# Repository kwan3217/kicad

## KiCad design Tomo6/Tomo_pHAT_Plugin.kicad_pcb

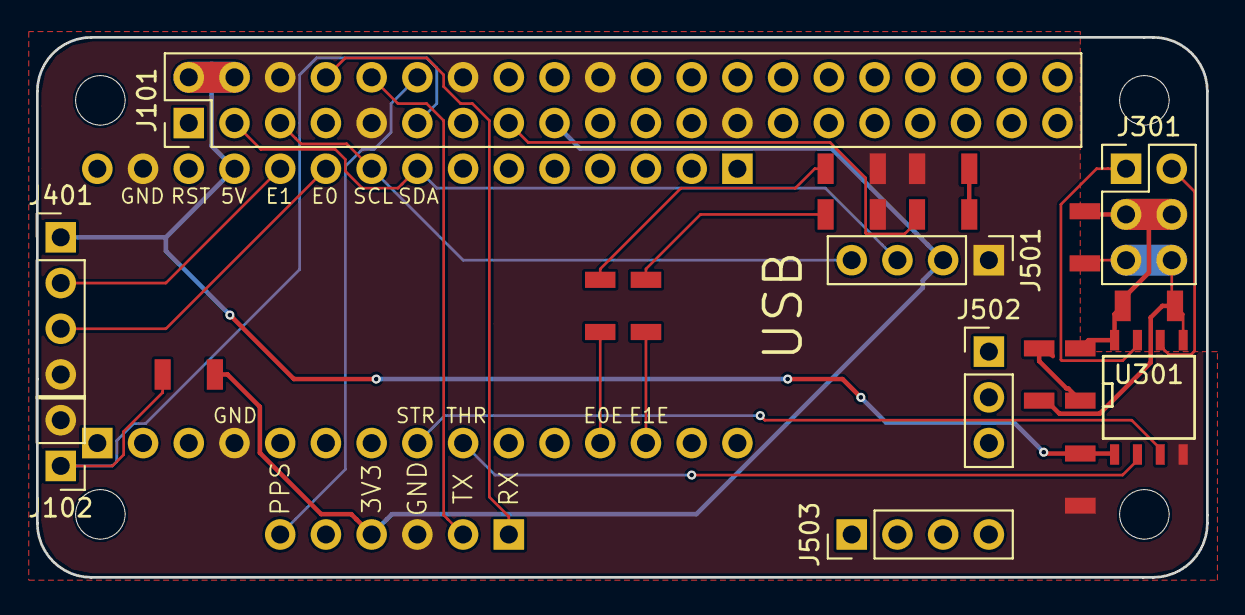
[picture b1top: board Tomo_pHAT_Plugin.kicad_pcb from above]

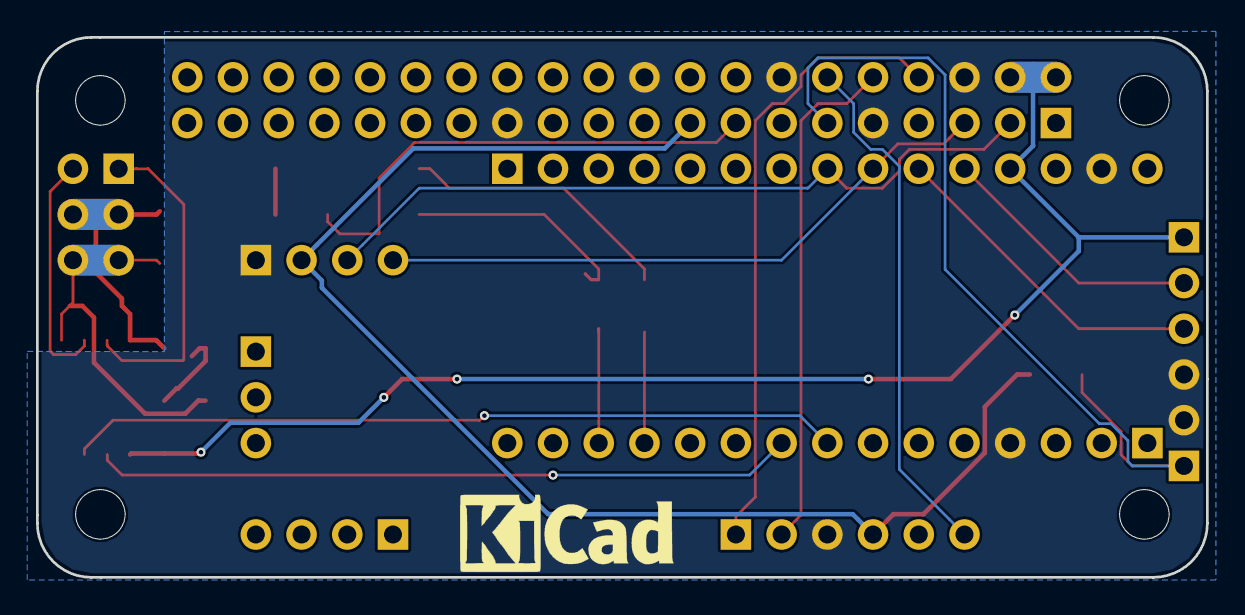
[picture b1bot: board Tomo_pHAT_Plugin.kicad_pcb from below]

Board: 2 copper layers, 65.0 x 30.0 mm, 28 parts (2 on the bottom side), 24 nets.

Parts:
1PIN, 1PIN#2, 1PIN#3, 1PIN#4: P***; 1pin
C301, C305: 100nF; SMD_1206
C308: 10uF; SMD_1206
D112: RED; D_1206
D308: BLUE; D_1206
D409: GREEN; D_1206
D410: YELLOW; D_1206
J101: RPi_GPIO; Pin_Header_Straight_2x20_Pitch2.54mm
J102: CONN_01X02; Socket_Strip_Straight_1x02_Pitch2.54mm
J301: CONN_02X03; Pin_Header_Straight_2x03_Pitch2.54mm
J401, J501, J503: CONN_01X04; Pin_Header_Straight_1x04_Pitch2.54mm
J502: CONN_01X03; Pin_Header_Straight_1x03_Pitch2.54mm
J601: CONN_01X04; GPSFeatherWing
R112, R308, R409, R410: 220; SMD_1206
R117: 10k; SMD_1206
U001: Designed_With_Kicad; Symbol_KiCAD-Logo_CopperAndSilkScreenTop
U002: KwanSystems; KWAN_CIRCLE_soldermask
U301: ADuM3221; SOIC-8-N
U401: Arduino_Nano; ArduinoNano

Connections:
+3V3: J101.17, J501.2, J601.4, R117.2
+5V: C301.1, J101.2, J101.4, J401.1, U301.1, U401.27
+BATT: C305.1, C308.1, D308.2, J301.3, J301.4, U301.8
/BATPWR-: D308.1, R308.1
/E0_ECHO: R409.1, U401.12
/E0_ECHO-: D409.2, R409.2
/E1_ECHO: R410.1, U401.13
/E1_ECHO-: D410.2, R410.2
/ENCODER0: J401.3, U401.25
/ENCODER1: J401.2, U401.26
/GO_BTN: J101.11, J102.1, R117.1
/GPS_RX: J101.8, J601.1
/GPS_TX: J101.10, J601.2
/PPS: J101.12, J601.6
/PPS_ECHO: J101.15, R112.1
/PPS_ECHO-: D112.2, R112.2
/SCL: J101.5, J501.4, U401.24
/SDA: J101.3, J501.3, U401.23
/STEER: U301.3, U401.8
/STEER_HI: J301.2, U301.6
/THROTTLE: U301.2, U401.9
/THROTTLE_HI: J301.1, U301.7
GND: C301.2, D112.1, D409.1, D410.1, J101.6, J101.9, J101.14, J101.20, J101.25, J102.2, J401.4, J501.1, J601.3, U301.4, U401.4, U401.29
GNDPWR: C305.2, C308.2, J301.5, J301.6, R308.2, U301.5

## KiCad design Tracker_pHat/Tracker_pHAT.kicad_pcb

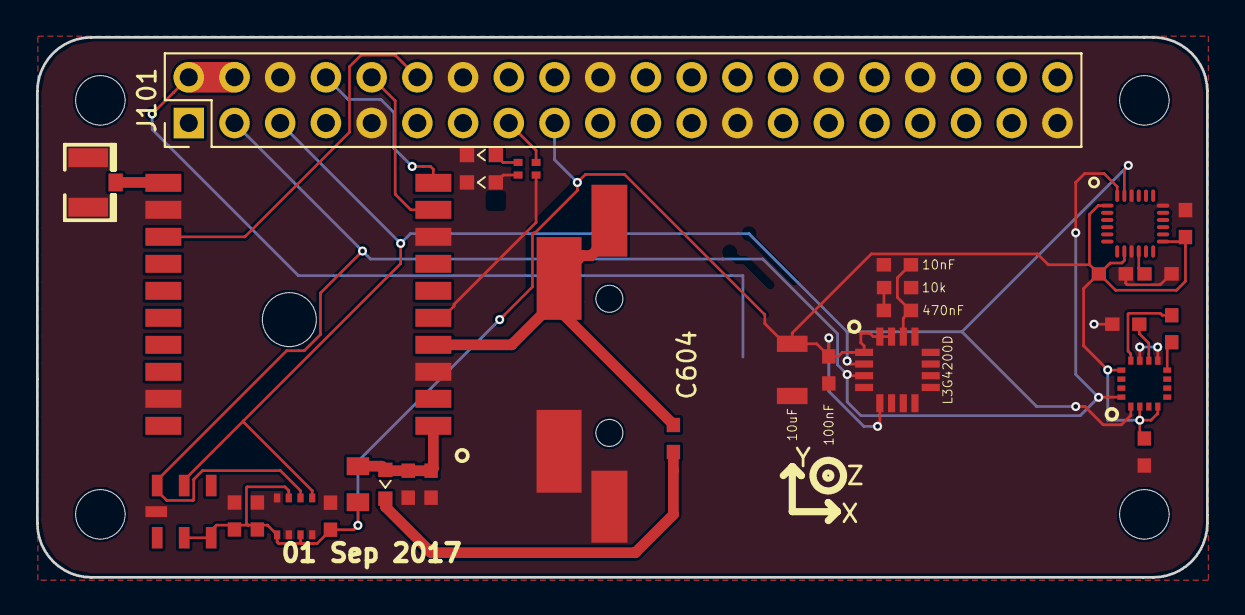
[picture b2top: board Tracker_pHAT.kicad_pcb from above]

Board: 2 copper layers, 65.0 x 30.0 mm, 37 parts (0 on the bottom side), 22 nets.

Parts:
1PIN, 1PIN#2, 1PIN#3, 1PIN#4: P***; 1pin
B604: Coin_Cell; CR1220-2
C508, C510, C513, C601, C702, C802, C806, C808, C901: 100nF; SMD_0603
C603: 10uF; SMD_0603
C604: 220mF; Supercap
C708: 220nF; SMD_0603
C710: 4.7uF; SMD_0603
C913: 10nF; SMD_0603
C914: 470nF; SMD_0603
C916: 10uF; SMD_1206
D115, D613: RED; D_0603
D604: D_Schottky; D_0603
J101: RPi_GPIO; Pin_Header_Straight_2x20_Pitch2.54mm
L601: Ferrite; SMD_0805
R122: 680; R_Array_Convex_2x0402
R604, R914: 10k; SMD_0603
U501: MPU9250; QFN24_PAD
U599: MPU9250; Axis
U601: FGPMMOPA6H
U701: HMC5883L
U801: BMP180
U802: BME280
U901: L3G4200D
X611: uFL; U.FL

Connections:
+3V3: C508.2, C513.2, C702.2, C802.2, C806.2, C808.2, C901.2, C916.2, J101.17, L601.1, U501.1, U501.8, U501.13, U701.2, U701.4, U701.13, U801.2, U801.3, U802.2, U802.6, U802.8, U901.1, U901.5, U901.15, U901.16
+5V: J101.2, J101.4
/FIX: R122.1, U601.5
/FIX+: D613.2, R122.4
/GPS_RX: J101.8, U601.10
/GPS_TX: J101.10, U601.9
/HMC5883/C1: C710.2, U701.10
/HMC5883/SETC: C708.2, U701.12
/HMC5883/SETP: C708.1, U701.8
/L3G4200D/PLLFILT: C913.2, C914.2, U901.14
/L3G4200D/PLLFILT-: C914.1, R914.1
/MPU9250/REGOUT: C510.2, U501.10
/PPS: J101.12, U601.13
/PPS_ECHO: J101.15, R122.2
/PPS_ECHO+: D115.2, R122.3
/SCL: J101.5, U501.23, U701.1, U801.5, U802.4, U901.2
/SDA: J101.3, U501.24, U701.16, U801.6, U802.3, U901.3
/UltimateGPS/ANT: U601.11, X611.3
/UltimateGPS/VBACKUP: B604.+, C604.1, R604.1, U601.4
/UltimateGPS/VBACKUP+: D604.1, R604.2
/UltimateGPS/VGPS: C601.2, C603.2, D604.2, L601.2, U601.1
GND: B604.-, C508.1, C510.1, C513.1, C601.1, C603.1, C604.2, C702.1, C710.1, C802.1, C806.1, C808.1, C901.1, C913.1, C916.1, D115.1, D613.1, J101.6, J101.9, J101.14, J101.20, J101.25, J101.30, J101.34, J101.39, R914.2, U501.9, U501.18, U501.22, U601.3, U601.8, U601.12, U601.19, U701.9, U701.11, U801.7, U802.1, U802.5, U802.7, U901.4, U901.8, U901.9, U901.10, U901.11, U901.12, U901.13, X611.1, X611.2

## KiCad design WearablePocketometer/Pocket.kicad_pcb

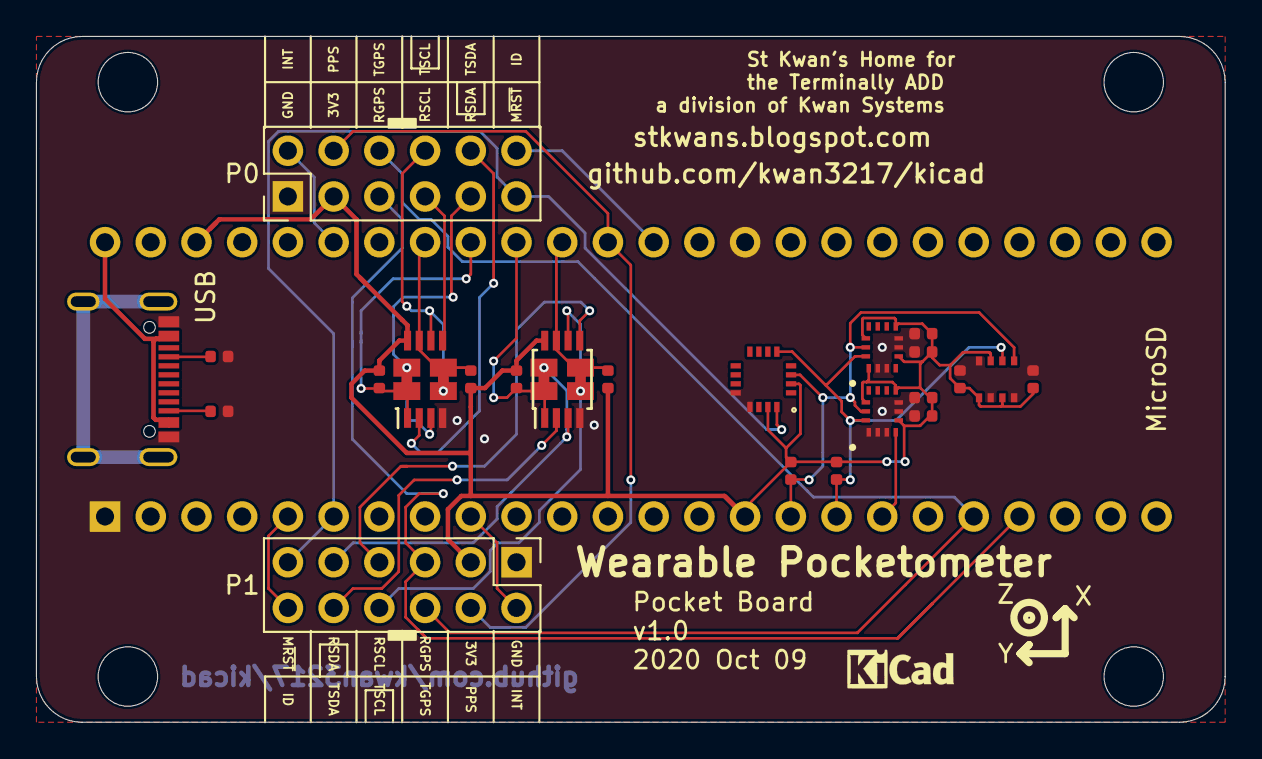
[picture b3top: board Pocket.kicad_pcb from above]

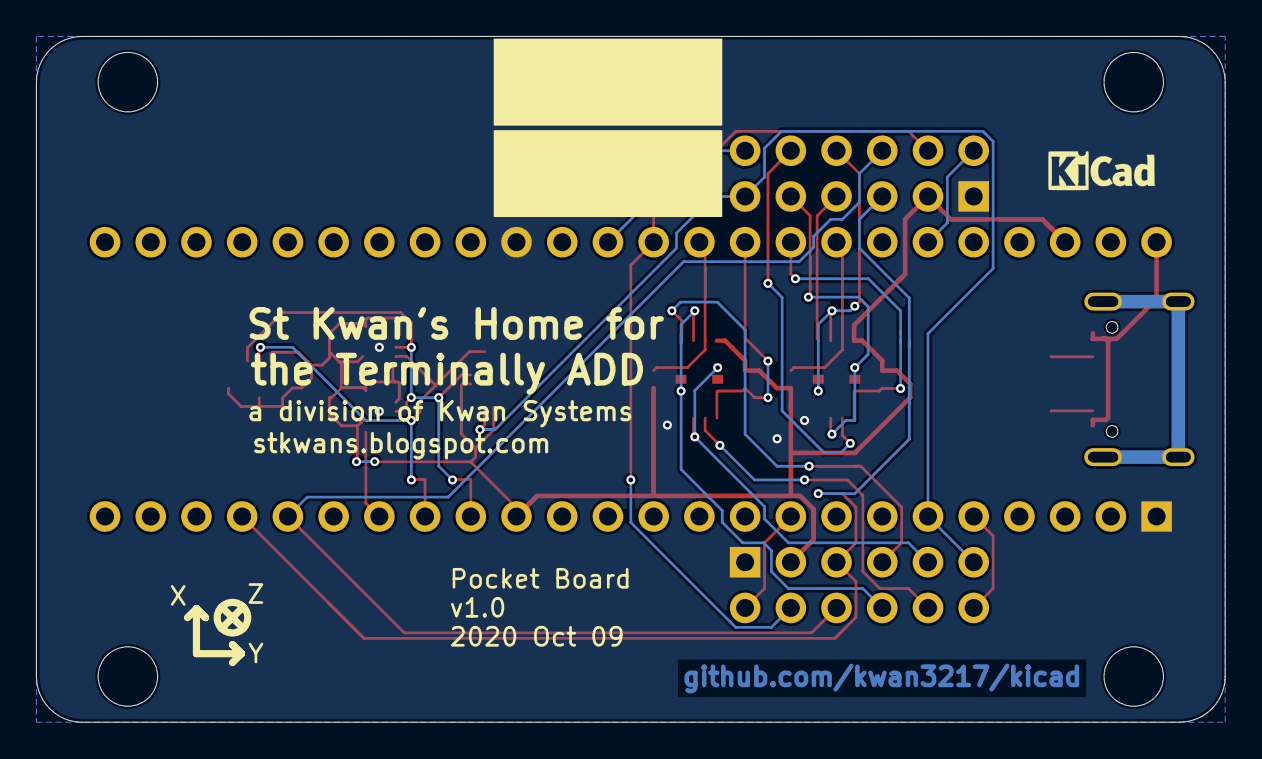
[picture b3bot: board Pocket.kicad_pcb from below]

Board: 2 copper layers, 66.0 x 38.1 mm, 38 parts (3 on the bottom side), 28 nets.

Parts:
C905, C908, C1005, C1008, C1106, C1108: 100nF; C_0402_1005Metric
G101, G101#2: DesignedWithKicad; Symbol_KiCAD-Logo_CopperAndSilkScreenTop_small
G102, G104: KwanSystems; StKwansSoldermask
G103: OSHW; OSHW-Symbol_6.7x6mm_SolderMask
G105: Axis
J101, J107, J111, J117: SolderJumper_2_Bridged; SolderJumper-2_Bridged
J102, J112: Conn_02x06_Male; PinHeader_2x06_P2.54mm_Vertical
J120, J125, J127, J129: STANDOFF; STANDOFF_NONPLATED
J1601: USB_C_Receptacle_USB2.0; GCTUSBTypeC_PTH
R116, R117, R138, R139, R140, R141: 10k; R_0402_1005Metric
R1601, R1602: 5.1k; R_0402_1005Metric
U101: AK09970
U102, U112: P82B96; TSSOP-8_3x3mm_P0.65mm
U104: Teensy4.1; Teensy2x24
U901, U1001: LSM6DSO; LGA-14L
U1101: BME280

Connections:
+3V3: C905.1, C908.1, C1005.1, C1008.1, C1106.1, C1108.2, J102.3, J112.3, R116.1, R117.1, R138.2, R139.2, R140.2, R141.2, U101.2, U101.15, U102.8, U104.15, U104.46, U112.8, U901.5, U901.8, U901.12, U1001.1, U1001.5, U1001.8, U1001.12, U1101.2, U1101.6, U1101.8
+5V: J1601.A4, J1601.A9, J1601.B4, J1601.B9, U104.48
/MAG~RST: J102.11, J112.11, U101.16, U104.6
/P0_ID: J112.12, U104.36
/P0_INT: J112.2, U104.43
/P0_RX_SCL: J112.7, U112.5
/P0_RX_SDA: J111.1, J112.9, U112.3
/P0_SCL: J117.2, R141.1, U104.41, U112.7
/P0_SDA: J111.2, R140.1, U104.40, U112.1
/P0_TX_SCL: J112.8, J117.1, U112.6
/P0_TX_SDA: J112.10, U112.2
/P1_ID: J102.12, U104.5
/P1_INT: J102.2, U104.9
/P1_RX_SCL: J102.7, U102.5
/P1_RX_SDA: J101.1, J102.9, U102.3
/P1_SCL: J107.2, R138.1, U102.7, U104.38
/P1_SDA: J101.2, R139.1, U102.1, U104.39
/P1_TX_SCL: J102.8, J107.1, U102.6
/P1_TX_SDA: J102.10, U102.2
/P2_INT: U104.18, U901.4
/P2_SCL: R116.2, U101.3, U104.16, U901.13, U1001.13, U1101.4
/P2_SDA: R117.2, U101.5, U104.17, U901.14, U1001.14, U1101.3
/PPS: J102.4, J112.4, U104.37
/RX_GPS: J102.5, J112.5, U104.21
/TX_GPS: J102.6, J112.6, U104.20
/USB C Power/CC1: J1601.A5, R1601.1
/USB C Power/CC2: J1601.B5, R1602.1
GND: C905.2, C908.2, C1005.2, C1008.2, C1106.2, C1108.1, J102.1, J112.1, J1601.A1, J1601.A12, J1601.B1, J1601.B12, R1601.2, R1602.2, U101.12, U101.13, U102.4, U104.1, U104.34, U112.4, U901.1, U901.2, U901.3, U901.6, U901.7, U1001.2, U1001.3, U1001.6, U1001.7, U1101.1, U1101.5, U1101.7

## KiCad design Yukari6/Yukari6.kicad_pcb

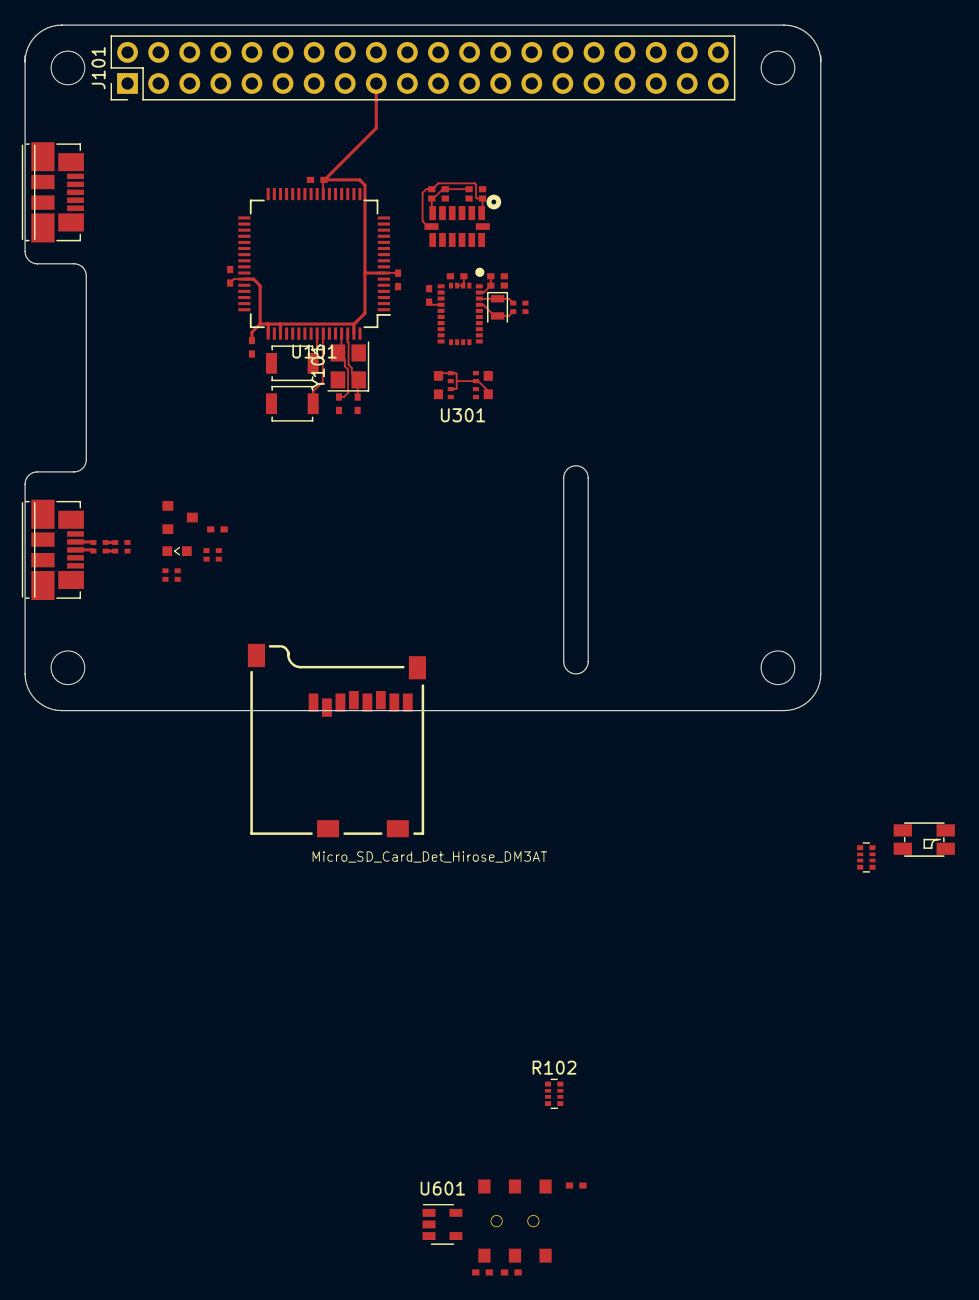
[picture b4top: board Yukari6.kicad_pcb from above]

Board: 2 copper layers, 65.0 x 56.0 mm, 44 parts (0 on the bottom side), 39 nets.

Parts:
C107, C123, C143, C151, C203, C209, C401, C405, C604: 100nF; SMD_0402
C161, C162: 33pF; SMD_0402
C225: 120nF; SMD_0402
C226, C523: 22pF; R_Array_Convex_2x0402
C228: 6.8nF; SMD_0402
C306, C308: 100nF; SMD_0603
C406, C601: 1uF; SMD_0402
C605: 4.7nF; SMD_0402
D101: HSMF-C118
D550: BLUE; D_0603
J101: RPi_GPIO; Pin_Header_Straight_2x20_Pitch2.54mm
J501, J502: USB_MICROB; USB_Micro-B_Molex_47346-0001
J701: Micro_SD_Card_Det_Hirose_DM3AT; MICROSD-SOCKET-PP
Q550: PMOS; SOT-23
R101: 10k; R_Array_Convex_4x0402
R102: 1.5k; R_Array_Convex_4x0402
R406: 100; SMD_0402
R511: 22k; SMD_0402
R523: 33; R_Array_Convex_2x0402
R550: 1.5k; R_Array_Convex_2x0402
R551: 10k; R_Array_Convex_2x0402
S157: SPST; SW_SPST_B3U-1000P
S158: B3U-1000P; SW_SPST_B3U-1000P
S603: SPDT; SWITCH_DPDT_AZY0202
U101: LPC2148; LQFP-64_10x10mm_Pitch0.5mm
U202: BNO055
U301: BME280
U401: ADXL375
U601: 3.3V; SOT-23-5
Y101: 12MHz; Crystal_SMD_Abracon_ABM8G-4pin_3.2x2.5mm
Y201: 32kiHz; Crystal_SMD_2012-2pin_2.0x1.2mm

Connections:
/ACCINT: U101.46, U202.14
/BSL: R101.1, U101.41
/CS0: J701.2, U101.45
/DB: D101.4, R102.2
/DG: D101.3, R102.1
/DR: D101.2, R102.4
/HIACCINT: U101.2, U401.8
/HighAcc/SCL: U202.19, U301.4, U401.14
/HighAcc/VS: C405.1, C406.1, R406.2, U401.6
/MISO0: J701.7, U101.29
/MOSI0: J701.3, U101.30
/Orientation/CAP: C209.1, U202.9
/Orientation/XIN32: C226.1, U202.27, Y201.1
/Orientation/XOUT32: C226.2, U202.26, Y201.2
/PPS: J101.12, U101.47
/PWMB: R102.7, U101.1
/PWMG: R102.8, U101.31
/PWMR: R102.5, U101.33
/RST: R101.2, S157.2, U101.57
/RX0: J101.8, U101.21
/Regulator/BYP: C604.1, U601.4
/Regulator/PWR_EN: S603.2, U601.3
/SCK0: J701.5, U101.27
/SCL0: J101.5, R101.4, U101.22
/SDA0: J101.3, R101.3, U101.26, U202.20, U301.3, U401.13
/TX0: J101.10, U101.19
/USB/CONN_D+: J501.3, R523.4, R550.1
/USB/CONN_D-: J501.2, R523.3
/USB/USB_LIGHT+: Q550.3, R550.3, R550.4
/USB/USB_LIGHT-: D550.2, R550.2
/USB_D+: C523.2, R523.1, U101.10
/USB_D-: C523.1, R523.2, U101.11
/USB_ON: R511.2, R551.1, S158.1, U101.58
/USB_SOFTCONNECT: Q550.1, R551.3, U101.17
/VBUS: C601.1, J101.2, J101.4, J501.1, J502.1, R551.4, S603.1, U601.1
/XTAL1: C162.2, U101.62, Y101.1
/XTAL2: C161.2, U101.61, Y101.3
GND: C107.2, C123.2, C143.2, C151.2, C161.1, C162.1, C203.1, C209.2, C225.2, C226.3, C226.4, C228.2, C306.1, C308.1, C401.2, C405.2, C406.2, C523.3, C523.4, C601.2, C604.2, C605.2, D550.1, J101.6, J101.9, J101.14, J101.20, J101.25, J101.30, J101.34, J101.39, J501.5, J501.6, J502.5, J502.6, J701.6, J701.9, R511.1, S157.1, S158.2, S603.3, U101.6, U101.18, U101.25, U101.42, U101.50, U101.59, U202.2, U202.5, U202.6, U202.15, U202.16, U202.17, U202.18, U202.25, U301.1, U301.5, U301.7, U401.2, U401.4, U401.5, U401.12, U601.2, Y101.2, Y101.4
VCC: C107.1, C123.1, C143.1, C151.1, C203.2, C225.1, C228.1, C306.2, C308.2, C401.1, C605.1, D101.1, J101.1, J101.17, J701.4, Q550.2, R101.5, R101.6, R101.7, R101.8, R406.1, R551.2, U101.7, U101.23, U101.43, U101.49, U101.51, U101.63, U202.3, U202.4, U202.11, U202.28, U301.2, U301.6, U301.8, U401.1, U401.7, U601.5

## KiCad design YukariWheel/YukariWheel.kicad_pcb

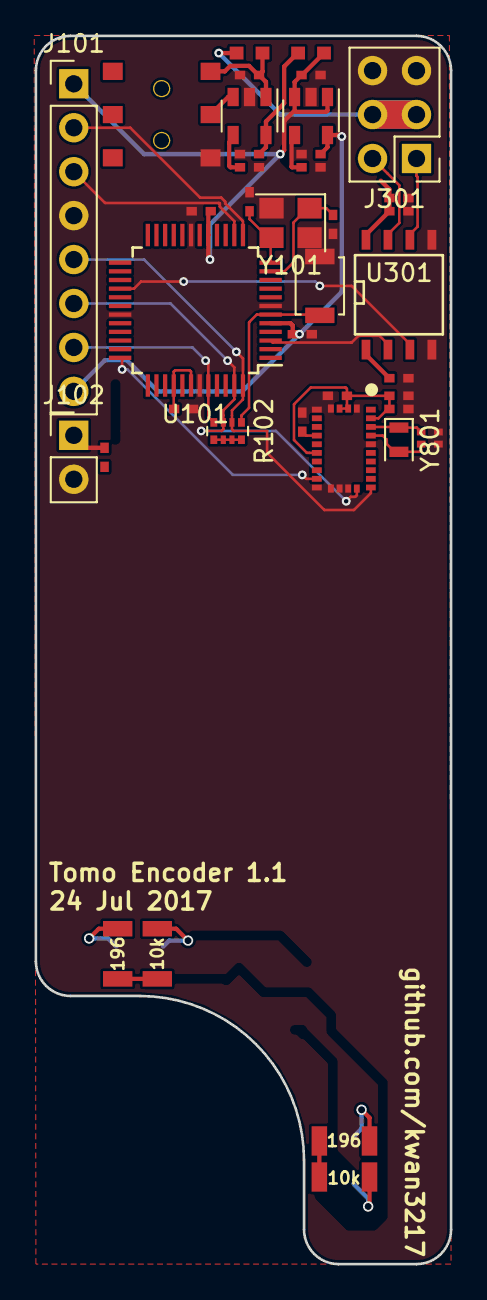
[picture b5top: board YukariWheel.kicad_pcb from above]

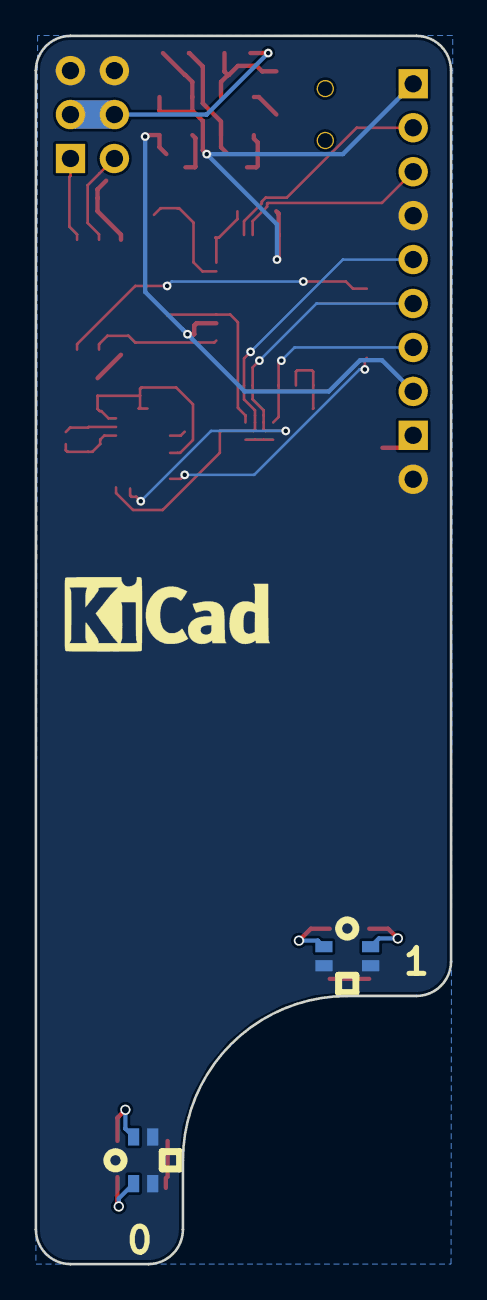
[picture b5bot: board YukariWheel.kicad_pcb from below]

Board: 2 copper layers, 24.0 x 71.0 mm, 43 parts (3 on the bottom side), 30 nets.

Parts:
C105, C117, C204, C301, C305, C404, C803, C809: 100nF; SMD_0402
C111, C112: 33pF; SMD_0402
C140, C201, C401: 1uF; SMD_0402
C205, C405: 4.7nF; SMD_0402
C308: 10uF; SMD_0402
C825: 120nF; SMD_0402
C826: 22pF; R_Array_Convex_2x0402
C828: 6.8nF; SMD_0402
J101: Conn_01x08; Pin_Header_Straight_1x08_Pitch2.54mm
J102: CONN_01X02; Socket_Strip_Straight_1x02_Pitch2.54mm
J301: CONN_02X03; Pin_Header_Straight_2x03_Pitch2.54mm
L201, L401: Ferrite_Bead_Small; SMD_0603
R001, R101: 196; SMD_1206
R003, R103: 10k; SMD_1206
R102: 10k; R_Array_Convex_4x0402
R117: 10k; SMD_0402
S157: SPST; SW_SPST_B3U-1000P
S401: SPDT; SWITCH_DPDT_AZY0202
U000, U100: EE-SY199
U001: Designed_With_Kicad; Symbol_KiCAD-Logo_CopperAndSilkScreenTop
U002: KwanSystems; KWAN_CIRCLE_soldermask
U101: LPC2103; LQFP-48_7x7mm_Pitch0.5mm
U201: 1.8V; SOT-23-5
U301: ADuM3221; SOIC-8-N
U401: 3.3V; SOT-23-5
U801: BNO055
Y101: 12MHz; Crystal_SMD_Abracon_ABM8G-4pin_3.2x2.5mm
Y801: 32kiHz; Crystal_SMD_2012-2pin_2.0x1.2mm

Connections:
+1V8: C105.1, C205.1, J101.8, U101.5, U201.5
+3V3: C117.1, C140.1, C201.1, C301.1, C803.2, C825.1, C828.1, J101.1, L201.1, R001.1, R003.1, R101.1, R102.5, R102.6, R102.7, R102.8, R103.1, R117.2, U101.4, U101.17, U101.40, U101.42, U201.1, U201.3, U301.1, U801.3, U801.4, U801.11, U801.28
+BATT: C305.1, C308.1, J301.3, J301.4, L401.2, U301.8
/3V3+: C405.1, L201.2, U401.5
/ACCINT: U101.36, U801.14
/BNO055/CAP: C809.1, U801.9
/BNO055/XIN32: C826.1, U801.27, Y801.1
/BNO055/XOUT32: C826.2, U801.26, Y801.2
/BSL: J101.7, R102.4, U101.44
/D0: R001.2, U000.1
/D1: R101.2, U100.1
/ENC0: R003.2, U000.3, U101.32
/ENC1: R103.2, U100.3, U101.33
/GO_BTN: J102.1, R117.1
/RST: R102.1, S157.2, U101.6
/RX0: J101.3, U101.14
/Regulator1V8/BYP: C204.1, U201.4
/Regulator3V3/BYP: C404.1, U401.4
/Regulator3V3/PWR_EN: S401.2, U401.3
/SCL: J101.6, R102.3, U101.47, U801.19
/SDA: J101.5, R102.2, U101.48, U801.20
/STEERING: U101.28, U301.3
/STEER_HI: J301.1, U301.6
/THROTTLE: U101.3, U301.2
/THROTTLE_HI: J301.2, U301.7
/TX0: J101.2, U101.13
/VBAT-: C401.1, L401.1, S401.1, U401.1
/XTAL1: C111.2, U101.11, Y101.1
/XTAL2: C112.2, U101.12, Y101.3
GND: C105.2, C111.1, C112.1, C117.2, C140.2, C201.2, C204.2, C205.2, C301.2, C305.2, C308.2, C401.2, C404.2, C405.2, C803.1, C809.2, C825.2, C826.3, C826.4, C828.2, J101.4, J102.2, J301.5, J301.6, S157.1, S401.3, U000.2, U000.4, U100.2, U100.4, U101.7, U101.19, U101.31, U101.43, U201.2, U301.4, U301.5, U401.2, U801.2, U801.5, U801.6, U801.15, U801.16, U801.17, U801.18, U801.25, Y101.2, Y101.4

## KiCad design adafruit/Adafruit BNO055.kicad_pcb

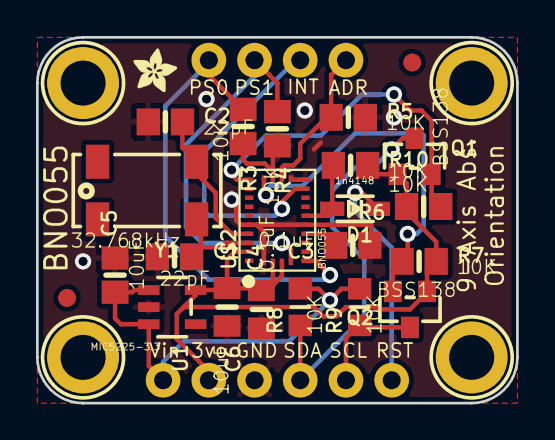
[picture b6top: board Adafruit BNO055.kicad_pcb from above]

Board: 2 copper layers, 26.7 x 20.3 mm, 31 parts (0 on the bottom side), 16 nets.

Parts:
C1, C2: 22pF; 0805-NO
C3: 0.1uF; 0805-NO
C4: 0.1uF; 0805_10MGAP
C5: 10uF; 0805-NO
C6: 10uF; 0805_10MGAP
D1: 1n4148; SOD-323
FID1, FID2: FIDUCIAL; FIDUCIAL_1MM
JP1: 1X06_ROUND_76
JP2: 1X04_ROUND_76
Q1, Q2: BSS138; SOT23-WIDE
R3, R4, R5, R6, R7, R10: 10K; 0805-NO
R8, R9: 10K; _0805MP
U1: MIC5225-3.3; SOT23-5
U$2: BNO055
U$3: PCBFEAT-REV-040
U$28: ADAFRUIT_TEXT_20MM
U$29, U$30, U$31, U$32: MOUNTINGHOLE2.5_THICK; MOUNTINGHOLE_2.5_PLATED_THICK
U$33: ADAFRUIT_2.5MM
Y1: 32.768kHz; CRYSTAL_8X3.8

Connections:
3.3V: C4.2, C6.1, JP1.2, Q1.1, Q2.1, R6.2, R7.2, R10.2, U1.5, U$2.3, U$2.4, U$2.28
5.0V: C5.1, JP1.1, R8.2, R9.2, U1.1, U1.3
GND: C1.1, C2.1, C3.1, C4.1, C5.2, C6.2, JP1.3, R3.2, R4.2, R5.2, U1.2, U$2.2, U$2.10, U$2.15, U$2.16, U$2.18, U$2.25
I2CADDR_3V: JP2.4, R5.1, U$2.17
INT_3V: JP2.3, U$2.14
unnamed: C1.2, U$2.27, Y1.P$4
unnamed: C2.2, U$2.26, Y1.P$1
unnamed: C3.2, U$2.9
NRESET_3V: D1.A, R10.1, U$2.11
PS0_3V: JP2.1, R3.1, U$2.6
PS1_3V: JP2.2, R4.1, U$2.5
RST_5V: D1.C, JP1.6
SCL_3V: Q2.2, R7.1, U$2.19
SCL_5V: JP1.5, Q2.3, R9.1
SDA_3V: Q1.2, R6.1, U$2.20
SDA_5V: JP1.4, Q1.3, R8.1

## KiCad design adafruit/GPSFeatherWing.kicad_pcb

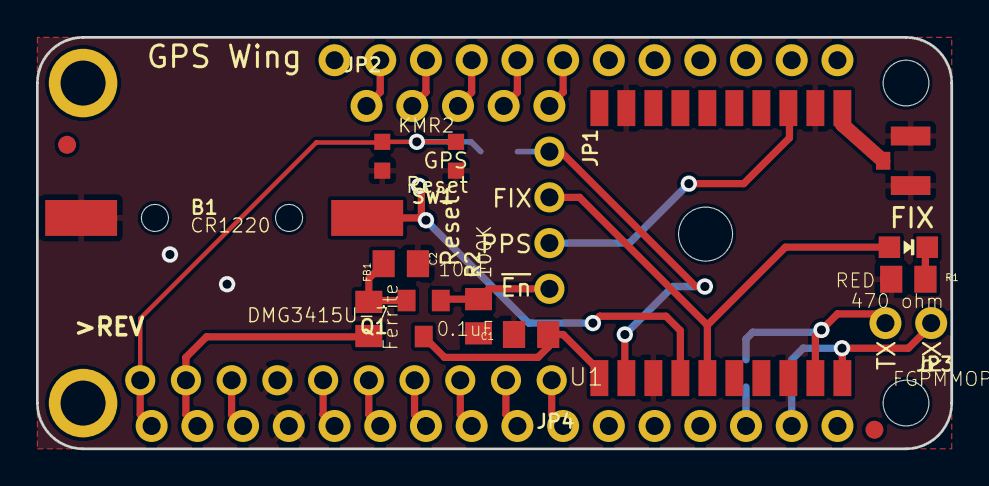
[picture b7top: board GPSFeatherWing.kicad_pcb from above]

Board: 2 copper layers, 50.8 x 22.9 mm, 25 parts (0 on the bottom side), 28 nets.

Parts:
B1: CR1220; CR1220-2
C1: 0.1uF; 0805-NO
C2: 10uF; 0805-NO
FB1: Ferrite; 0805-NO
FID1, FID2: FIDUCIAL; FIDUCIAL_1MM
JP1: 1X04_ROUND
JP2: 1X05_ROUND_70
JP3: 1X02_ROUND
JP4: 1X10_ROUND
LED1: RED; CHIPLED_0805_NOOUTLINE
MS1: FEATHERWING
Q1: DMG3415U-7; SOT23-WIDE
R1: 470 ohm; 0805-NO
R2: 100K; 0805-NO
SJ1: SOLDERJUMPER_ARROW_NOPASTE
SJ2, SJ3: SOLDERJUMPER_CLOSEDWIRE
SW1: KMR2; BTN_KMR2_4.6X2.8
TP1: TESTPOINT_ROUND_1.5MM
U1: FGPMMOPA6H
U$9: PCBFEAT-REV-040
U$10: FEATHERLOGO
U$11: ADAFRUIT_TEXT_20MM
X1: uFL; U.FL

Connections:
1PPS: JP1.3, U1.P$13
3.3V: C2.1, FB1.2, Q1.2
3V: FB1.1, JP4.9, MS1.2
ENABLE: JP1.4, Q1.1, R2.2
FIX: JP1.2, LED1.A, U1.P$5
GND: B1.-, C1.2, C2.2, JP4.7, MS1.4, R1.1, R2.1, SW1.A, SW1.A', U1.P$3, U1.P$8, U1.P$12, U1.P$19, X1.1, X1.2
GRESET: JP1.1, SJ1.2, U1.P$2
unnamed: JP2.3, MS1.25
unnamed: LED1.C, R1.2
unnamed: JP2.4, MS1.24
unnamed: U1.P$11, X1.3
unnamed: JP2.5, MS1.23
unnamed: JP4.1, MS1.10
unnamed: JP4.2, MS1.9
unnamed: JP4.3, MS1.8
unnamed: JP4.4, MS1.7
unnamed: JP4.5, MS1.6
unnamed: JP4.6, MS1.5
unnamed: JP4.10, MS1.1, SJ1.1, SW1.B, SW1.B'
unnamed: JP4.8, MS1.3
unnamed: JP2.1, MS1.27
unnamed: C1.1, Q1.3, U1.P$1
unnamed: MS1.14, SJ2.2
unnamed: MS1.15, SJ3.2
RX: JP3.1, SJ3.1, U1.P$10
TX: JP3.2, SJ2.1, U1.P$9
USB: JP2.2, MS1.26
VBACKUP: B1.+, TP1.P$1, U1.P$4
